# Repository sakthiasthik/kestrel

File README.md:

# kestrel
18650 based Dc to DC board for 5v power source for the projects &amp; use as power bank also

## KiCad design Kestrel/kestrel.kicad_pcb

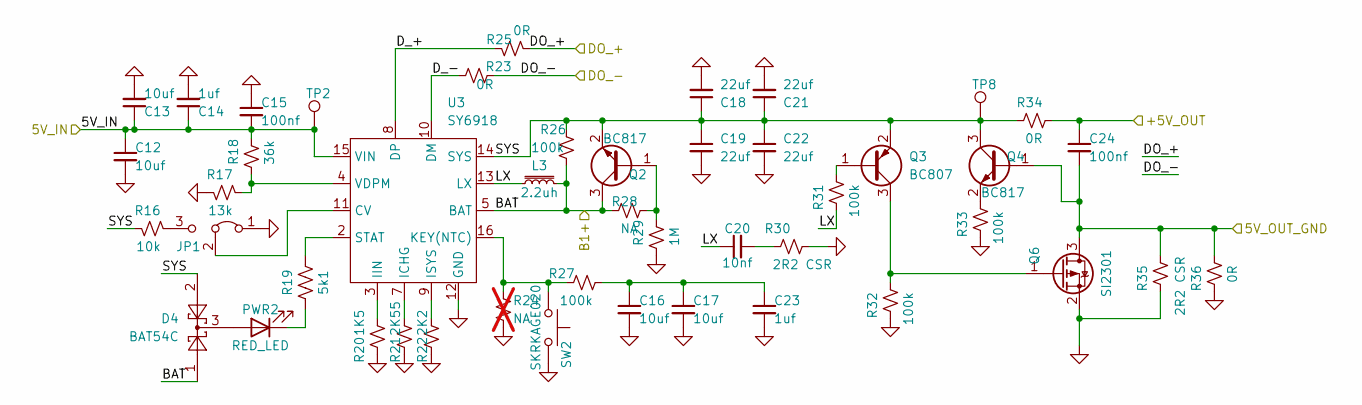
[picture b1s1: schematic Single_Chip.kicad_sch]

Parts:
C12, C13: 10uf; C_1206_3216Metric
C14, C23: 1uf; C_0603_1608Metric
C15, C24: 100nf; C_0603_1608Metric
C16, C17: 10uf; C_0805_2012Metric
C18, C19, C21, C22: 22uf; C_1206_3216Metric
C20: 10nf; C_0603_1608Metric
D4: BAT54C; SOT-23
JP1: Jumper_3_Bridged12; J_0402_1005Metric
L3: 2.2uh; L_APV_APH0650_6045
PWR2: RED_LED; LED_0805_2012Metric; Manufacturer_Part_Number MP006842; LCSC_Part C965812
Q2, Q4: BC817; SOT-23
Q3: BC807; SOT-23
Q6: SI2301; SOT-23; Manufacturer_Part_Number SI2301
R16: 10k; R_0603_1608Metric
R17: 13k; R_0603_1608Metric
R18: 36k; R_0603_1608Metric
R19: 5k1; R_0603_1608Metric; Manufacturer_Part_Number MCWR06X5101FTL; LCSC_Part C23186
R20: 1K5; R_0603_1608Metric
R21: 2K55; R_0603_1608Metric
R22: 2K2; R_0603_1608Metric
R23, R25, R34, R36: 0R; R_0603_1608Metric
R24: NA; R_0603_1608Metric; not fitted
R26, R27, R31, R32, R33: 100k; R_0603_1608Metric
R28: NA; R_0603_1608Metric
R29: 1M; R_0805_2012Metric
R30, R35: 2R2 CSR; R_1206_3216Metric
SW2: SKRKAGE020; SW_Push_SPST_NO_Alps_SKRK; Manufacturer_Part_Number SKRKAGE020; LCSC_Part C18077675
TP2, TP8: TestPoint; TestPoint_Pad_D1.0mm
U3: SY6918; SY6918A_QFN-16_3x3mm

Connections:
/5V_GND_OUT: C24.2, Q4.1 (B), Q6.3 (D), R35.2, R36.2; also elsewhere on the board
/5V_IN: C12.1, C13.1, C14.1, C15.2, R18.1, TP2.1, U3.15 (VIN); also elsewhere on the board
/5V_OUT: C24.1, R34.2; also elsewhere on the board
/B1+: D4.1, L3.2, Q2.3 (C), R26.2, R28.1, U3.5 (BAT), U3.6 (NA); also elsewhere on the board
/DO_+: R25.1; also elsewhere on the board
/DO_-: R23.2; also elsewhere on the board
/Single Chip/D_+: R25.2, U3.8 (DP)
/Single Chip/D_-: R23.1, U3.10 (DM)
/Single Chip/LX: C20.1, L3.1, R31.1, U3.13 (LX)
/Single Chip/SYS: C18.1, C19.1, C21.1, C22.1, D4.2, Q2.2 (E), Q3.2 (E), Q4.3 (C), R16.1, R26.1, R34.1, TP8.1, U3.14 (SYS)
GND: C12.2, C13.2, C14.2, C15.1, C16.2, C17.2, C18.2, C19.2, C21.2, C22.2, C23.2, JP1.1 (A), Q6.2 (S), R17.1, R20.2, R21.2, R22.2, R24.2, R29.2, R30.2, R32.1, R33.1, R35.1, R36.1, SW2.2, U3.12 (GND); also elsewhere on the board
unnamed: C16.1, C17.1, C23.1, R27.2
unnamed: C20.2, R30.1
unnamed: JP1.3 (B), R16.2
unnamed: JP1.2 (C), U3.11 (CV)
unnamed: D4.3, PWR2.2 (A)
unnamed: PWR2.1 (K), R19.1
unnamed: Q2.1 (B), R28.2, R29.1
unnamed: Q3.1 (B), R31.2
unnamed: Q3.3 (C), Q6.1 (G), R32.2
unnamed: Q4.2 (E), R33.2
unnamed: R21.1, U3.7 (ICHG)
unnamed: R20.1, U3.3 (IIN)
unnamed: R22.1, U3.9 (ISYS)
unnamed: R24.1, R27.1, SW2.1, U3.16 (KEY(NTC))
unnamed: R19.2, U3.1 (NA), U3.2 (STAT)
unnamed: R17.2, R18.2, U3.4 (VDPM)

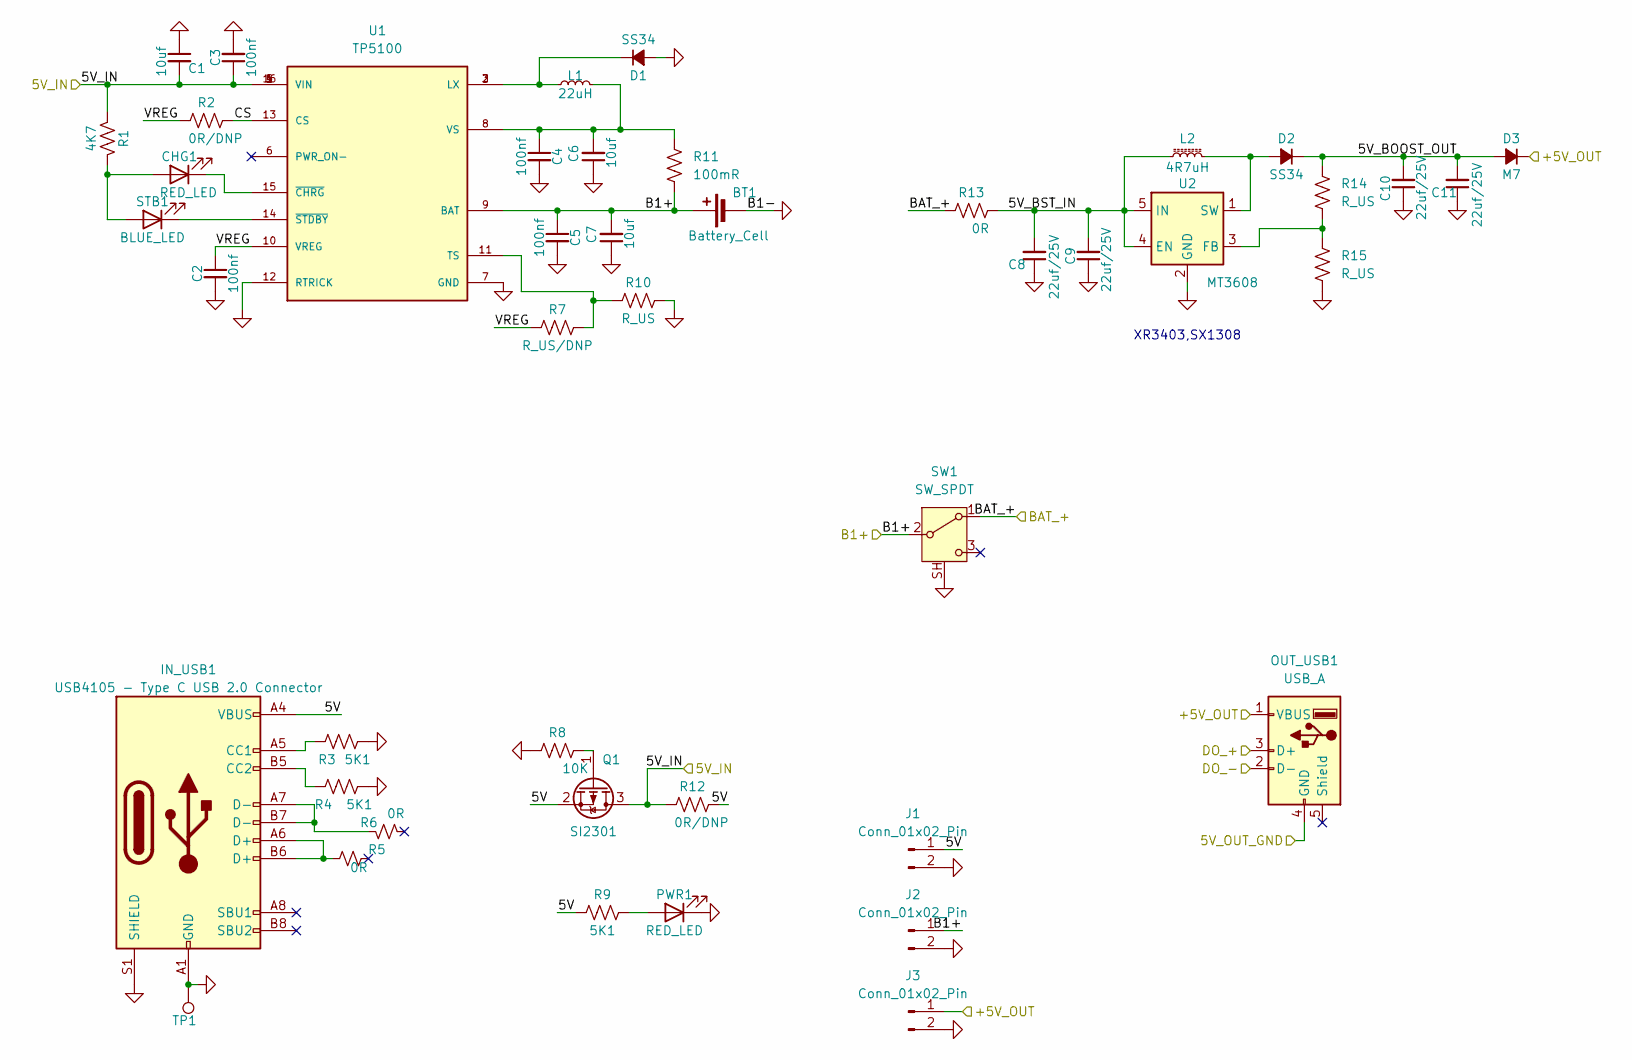
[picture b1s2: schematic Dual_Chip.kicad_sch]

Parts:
BT1: Battery_Cell; BatteryHolder_Keystone_1042_1x18650
C1, C6, C7: 10uf; C_0805_2012Metric; Manufacturer_Part_Number CL21A106KAYNNNG; LCSC_Part C15850
C2, C3, C4, C5: 100nf; C_0603_1608Metric; Manufacturer_Part_Number MC0603B104K250CT; LCSC_Part C14663
C8, C9, C10, C11: 22uf/25V; C_1206_3216Metric; Manufacturer_Part_Number CL31A226KAHNNNE; LCSC_Part C12891
CHG1: RED_LED; LED_0805_2012Metric; Manufacturer_Part_Number MP006842; LCSC_Part C965812
D1, D2: SS34; D_SMA
D3: M7; D_SMA
IN_USB1: USB4105 - Type C USB 2.0 Connector; USB_C_Receptacle_Palconn_UTC16-G; Manufacturer_Part_Number USB4105-15-A-120; LCSC_Part C2988369
J1, J2, J3: Conn_01x02_Pin; JST_EH_B2B-EH-A_1x02_P2.50mm_Vertical
L1: 22uH; L_APV_APH0650_6045
L2: 4R7uH; L_APV_APH0650_6045; Manufacturer_Part_Number ASPI-0630LR-4R7M; LCSC_Part C5189748
OUT_USB1: USB_A; USB_A_Type Female PCB R_A SMD
PWR1: RED_LED; LED_0805_2012Metric; Manufacturer_Part_Number MP006842; LCSC_Part C965812
Q1: SI2301; SOT-23; Manufacturer_Part_Number SI2301
R1: 4K7; R_0603_1608Metric; Manufacturer_Part_Number MCWR06X4701FTL; LCSC_Part C23162
R2, R12: 0R/DNP; R_0603_1608Metric; Manufacturer_Part_Number MCWR06X000 PTL; LCSC_Part C21189
R3, R4, R9: 5K1; R_0603_1608Metric; Manufacturer_Part_Number MCWR06X5101FTL; LCSC_Part C23186
R5, R6: 0R; R_0603_1608Metric
R7: R_US/DNP; R_0603_1608Metric
R8: 10K; R_0603_1608Metric; Manufacturer_Part_Number MCWR06X1002FTL; LCSC_Part C25804
R10, R14, R15: R_US; R_0603_1608Metric
R11: 100mR; R_1206_3216Metric
R13: 0R; R_0603_1608Metric; Manufacturer_Part_Number MCWR06X000 PTL
STB1: BLUE_LED; LED_0805_2012Metric; Manufacturer_Part_Number MP000442; LCSC_Part C965817
SW1: SW_SPDT; MSK-12C02
TP1: TestPoint; TestPoint_Pad_D1.0mm
U1: TP5100; QFN65P400X400X90-17N
U2: MT3608; SOT-23-6

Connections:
/5V_GND_OUT: OUT_USB1.4 (GND); also elsewhere on the board
/5V_IN: C1.2, C3.1, Q1.3 (D), R1.2, R12.1, U1.1 (VIN), U1.4 (VIN), U1.5 (VIN), U1.16 (VIN); also elsewhere on the board
/5V_OUT: D3.1 (K), J3.1, OUT_USB1.1 (VBUS); also elsewhere on the board
/B1+: BT1.+, C5.1, C7.2, J2.1, R11.2, SW1.2 (B), U1.9 (BAT); also elsewhere on the board
/DO_+: OUT_USB1.3 (D+); also elsewhere on the board
/DO_-: OUT_USB1.2 (D-); also elsewhere on the board
/Dual Chip/5V: IN_USB1.A4 (VBUS), IN_USB1.A9 (VBUS), IN_USB1.B4 (VBUS), IN_USB1.B9 (VBUS), J1.1, Q1.2 (S), R9.1, R12.2
/Dual Chip/5V_BOOST_OUT: C10.2, C11.2, D2.1 (K), D3.2 (A), R14.1
/Dual Chip/5V_BST_IN: C8.2, C9.2, L2.1, R13.2, U2.4 (EN), U2.5 (IN)
/Dual Chip/BAT_+: R13.1, SW1.1 (A)
/Dual Chip/CS: R2.2, U1.13 (CS)
/Dual Chip/VREG: C2.1, R2.1, R7.1, U1.10 (VREG)
GND: BT1.-, C1.1, C2.2, C3.2, C4.2, C5.2, C6.1, C7.1, C8.1, C9.1, C10.1, C11.1, D1.2 (A), IN_USB1.A1 (GND), IN_USB1.A12 (GND), IN_USB1.B1 (GND), IN_USB1.B12 (GND), IN_USB1.S1 (SHIELD), J1.2, J2.2, J3.2, PWR1.1 (K), R3.2, R4.2, R8.1, R10.2, R15.2, SW1.SH, TP1.1, U1.7 (GND), U1.12 (RTRICK), U1.17 (EXP), U2.2 (GND); also elsewhere on the board
unnamed: CHG1.2 (A), R1.1, STB1.2 (A)
unnamed: CHG1.1 (K), U1.15 (~CHRG)
unnamed: D1.1 (K), L1.1, U1.2 (LX), U1.3 (LX)
unnamed: D2.2 (A), L2.2, U2.1 (SW)
unnamed: IN_USB1.A5 (CC1), R3.1
unnamed: IN_USB1.B5 (CC2), R4.1
unnamed: IN_USB1.A6 (D+), IN_USB1.B6 (D+), R5.1
unnamed: IN_USB1.A7 (D-), IN_USB1.B7 (D-), R6.2
unnamed: PWR1.2 (A), R9.2
unnamed: Q1.1 (G), R8.2
unnamed: STB1.1 (K), U1.14 (~STDBY)
unnamed: R7.2, R10.1, U1.11 (TS)
unnamed: C4.1, C6.2, L1.2, R11.1, U1.8 (VS)
unnamed: R14.2, R15.1, U2.3 (FB)

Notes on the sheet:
XR3403,SX1308

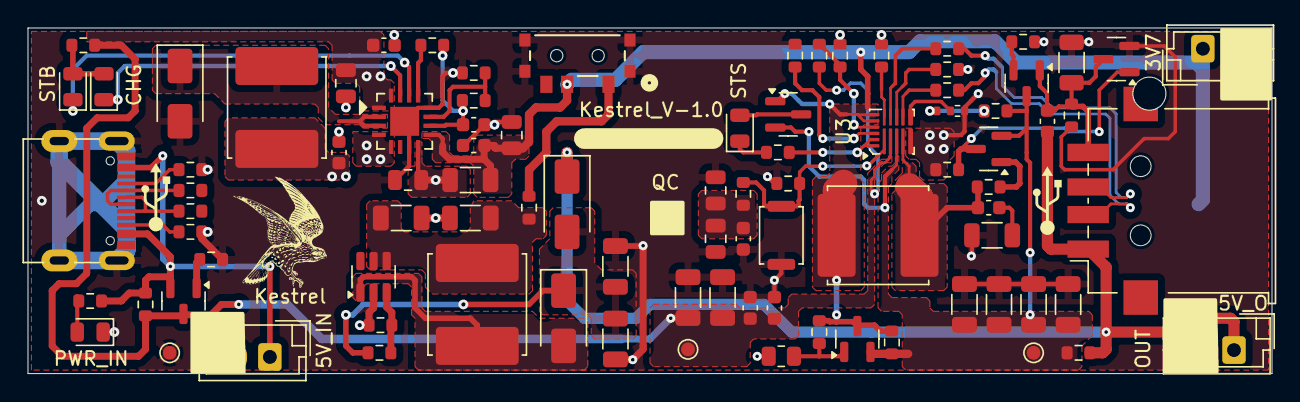
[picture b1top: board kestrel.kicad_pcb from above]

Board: 2 copper layers, 90.0 x 25.0 mm, 91 parts (1 on the bottom side), 47 nets.

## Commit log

2025-09-18 Initail commit for the desgin
2025-09-18 schematic added & other
2025-09-18 values updated in the tp circuit
2025-09-19 schematic updated
2025-09-24 new case design
2025-09-25 improved enclosure files
